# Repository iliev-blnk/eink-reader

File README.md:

# Cititor de cărți electronice cu e-ink

Proiect de licență, Universitatea „Ștefan cel Mare” din Suceava. Beleniuc Ilie, 2027.

Un cititor de cărți electronice cu ecran e-ink de 3,7″ și ESP32-S3, cu firmware
propriu, un format de carte propriu și placa lui proprie.

## Ce e aici

| dosar | ce e |
|---|---|
| [`firmware/`](firmware/) | firmware-ul ESP-IDF: driverul panoului, cardul, butoanele, managerul de aplicații, cititorul, somnul |
| [`spec/`](spec/) | formatul de carte (`.ibv`) și formatul de font (`.ibf`) |
| [`tools/`](tools/) | convertorul EPUB / FB2 / TXT → `.ibv`, unealta de fonturi, comparația cu TeX, fuzzerele, analiza jurnalului de timpi, înregistratorul de curent |
| [`sim/`](sim/) | simulatorul pe PC, cu testele cu imagini de referință |
| [`emu/`](emu/) | emulatorul: firmware-ul adevărat pe un ESP32-S3 emulat (QEMU) |
| [`hardware/`](hardware/) | schema prototipului, desenul plăcii de prototipare (`proto/`) și placa proprie (`pcb/`) |
| [`enclosure/`](enclosure/) | carcasa: model OpenSCAD parametric, cu placa citită din fișierul KiCad |
| [`measurements/`](measurements/) | experimentele: fișele de metodă, datele, figurile și rezultatele (E5 și E6 rulate până acum) |
| [`docs/`](docs/) | planul general, descrierea proiectului și jurnalul |

Planul, cu ce e gata și ce urmează: [`docs/MASTER-PLAN.md`](docs/MASTER-PLAN.md).
Jurnalul: [`docs/README.md`](docs/README.md).

## Unde e

Firmware-ul se compilează și rulează în emulator și în simulator. Încă n-a rulat
pe hardware: prototipul nu e lipit. Placa proprie e o ciornă, nerevizuită și
necomandată.

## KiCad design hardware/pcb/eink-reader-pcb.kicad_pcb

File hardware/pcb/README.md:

# Placa proprie v1 (CIORNĂ)

Placa cititorului care înlocuiește DevKit-ul și firele de pe masă: ESP32-S3,
încărcarea LiPo din USB-C, 3,3 V cu consum mic în somn, cardul și afișajul cu
alimentare comutată, trei butoane. Totul e **generat din script**: piesele și
legăturile sunt scrise o dată în `circuit.py`, din care ies schema, placa așezată
și trasată, verificările și fișierele pentru fabrică.

**E o ciornă.** Are revizia pe hârtie încheiată (PCB-4, [`REVIEW.md`](REVIEW.md));
nu s-a comandat. Codurile LCSC sunt verificate în catalog (PCB-5, mai jos); rotațiile și originile din `cpl.csv` sunt calculate din amprentele EasyEDA, dar nu sunt încă văzute în previzualizarea JLCPCB. Pașii PCB-1…3 din `docs/MASTER-PLAN.md` au acum o
primă variantă completă, cu trei luni înainte de calendar; prototipul de pe
DevKit rămâne referința până la măsurători.

## Cum se rulează

    hardware/pcb/make.sh                  # tot, ~2 min
    hardware/pcb/make.sh --fara-trasare   # doar verificările, fab/ și imaginile

Are nevoie de KiCad 10 (`kicad-cli` și modulul Python `pcbnew`), `cc` și `zip`.
`make.sh` se oprește dacă ERC-ul sau DRC-ul are vreo eroare, vreo legătură lipsă
sau vreo diferență între schemă și placă.

| fișier | ce face |
|---|---|
| `circuit.py` | sursa unică: piesele, valorile, amprentele, pinii pe rețele, codurile LCSC/MPN |
| `gen_sch.py` | schema `eink-reader-pcb.kicad_sch`, grupată pe blocuri, cu etichete globale |
| `gen_pcb.py` | placa: conturul, așezarea, rețelele, planurile, trasarea, umplerea zonelor |
| `route.py`, `astar.c` | trasorul (mai jos) |
| `project.py` | `.kicad_pro`: clasele de rețele și regulile |
| `eink-reader-pcb.kicad_dru` | regulile în plus (găurile butoanelor și ale mufei USB, traseele de putere) |
| `marking.py`, `usv_sigla.json` | serigrafia de pe spate: sigla USV și numele proiectului (mai jos) |
| `verifica.py` | regulile de proiectare pe care ERC/DRC nu le au: pinii ESP32-S3, polaritatea, decuplarea, antena, pinii din firmware (`--pini`: tabelul pin → rețea) |
| `REVIEW.md` | revizia PCB-4: fiecare bloc față de foaia lui de catalog, plus ce rămâne de hotărât |
| `jlc_rotatii.py`, `jlc_corectii.csv`, `test_jlc_rotatii.py` | corecțiile de rotație și origine pentru CPL, din amprentele EasyEDA, și verificarea lor pe o placă cu rotațiile confirmate de JLCPCB (vezi „Comanda”) |
| `make.sh` | tot lanțul, cu verificările |

Ies: `build/` (rapoartele ERC/DRC în JSON, poziții, BOM brut, `cupru.svg`),
`fab/` (gerbere + găuri în `gerber.zip`, `bom.csv` și `cpl.csv` în formatul
JLCPCB) și `img/`. `build/` și `fab/` nu intră în git; se refac oricând.

Schema și placa se deschid normal în KiCad, dar **nu se editează de mână**: o
schimbare se face în `circuit.py` sau în așezarea din `gen_pcb.py` și se rulează
din nou `make.sh`.

## Placa

- 105,79 × 53,80 mm, exact placa modulului de afișaj WeAct de 3,7 țoli, cu
  găurile de M2 în aceleași locuri: cele două stau spate în spate, cu
  distanțiere.
- 4 straturi (procesul JLCPCB): F.Cu semnale, In1.Cu plan GND întreg, In2.Cu
  plan +3V3, B.Cu semnale. Pe F.Cu și B.Cu, GND turnat în rest.
- Trasee și spații de 0,15 mm (procesul permite 0,1), via 0,6/0,3 mm.
  Rețelele de putere (VBUS, VSYS, VBAT, BAT_J, LX1, LX2, 3V3_SD, 3V3_EPD) au
  0,4 mm, cu 0,25 mm admis unde nu încape altfel (mai jos).
- Antena modulului ESP32 e pe marginea din dreapta; pe ultimii 6 mm ai plăcii
  (zona interzisă din amprenta modulului) nu e cupru pe niciun strat.

## Serigrafia

Pe spate (B.SilkS), fața fără piese: sigla Universității „Ștefan cel Mare” din
Suceava, „Proiect de licență”, numele, titlul și „2027 · placa v1”. Sigla e cea
de pe usv.ro, vectorizată cu potrace în `usv_sigla.json`. `marking.py` o pune
într-un grup care se înlocuiește la fiecare rulare (`python3 marking.py` merge și
pe placa deja trasată) și se oprește dacă ceva atinge o pastilă, o gaură sau o via.
Pe față nu e serigrafie în afară de contururile amprentelor: numele pieselor
stau pe F.Fab.

## Piesele

Codurile LCSC sunt verificate în catalogul JLCPCB (secțiunea „Comanda”);
fără cod au rămas doar baretele J3 și J5, care se lipesc de mână.

| bloc | piese | de ce |
|---|---|---|
| USB-C | J1 GCT USB4105, R1/R2 5,1 kΩ pe CC, U1 USBLC6-2SC6 (LCSC C7519), R17/R18 470 kΩ divizor VBUS → IO2 cu C17 100 nF, R25/R26 22 Ω serie pe D+/D− lângă modul | 5 V de la orice încărcător C; ESD pe D+/D−; firmware-ul vede când e cablul pus |
| încărcătorul | U2 BQ24074 (VQFN-16), R3 3,3 kΩ (ILIM ≈ 0,47 A), R4 1,8 kΩ (ICHG ≈ 0,5 A), R5 10 kΩ pe TS, D1/D2 PGOOD/CHG | power-path: dispozitivul merge din USB cu bateria goală; EN1/EN2 legați pentru USB500 |
| bateria | J2 JST-PH 2 pini, JP1 punte de lipit (I_BAT), U6 MAX17048 (indicator ModelGauge, I2C), R15/R16 1 MΩ divizor VBAT → IO1 | JP1 tăiată = un ampermetru în serie cu bateria, pentru E3/E4 |
| 3,3 V | SW1 PCM12 (comutator pornit/oprit pe EN), U3 TPS63900 buck-boost, L1 2,2 µH, R8/R9 configurarea | 75 nA în gol și buck-boost: 3,3 V stabil de la 4,2 V până la 2,5 V din baterie |
| comutatoare de sarcină | U4/U5 TPS22917 pentru card (3V3_SD) și afișaj (3V3_EPD), C7/C8 1 nF urcare lentă, R10/R11 1 MΩ pe EN | cardul și panoul nu consumă nimic în somn |
| MCU | U7 ESP32-S3-WROOM-1-N16R8 (C2913202), RC pe EN, SW5 BOOT, SW6 RESET, J5 UART0 | același modul ca pe DevKit, deci aceeași hartă de pini |
| butoane | SW2–SW4 Alps SKRTLAE010 (C110293), pe margini (două pe stânga, MENIU sus), apăsate din lateral | ÎNAPOI, ÎNAINTE, MENIU |
| afișaj | J3 baretă 1×8 de 2,54 mm spre modulul WeAct | BUSY, RST, DC, CS, SCK, MOSI, GND, 3V3_EPD; SCK și MOSI sunt ale lui, nu le împarte cu cardul |
| card | J4 Molex 104031 microSD, R21–R24 47 kΩ | modul SPI; pull-up pe CS, MISO și DAT1/DAT2 |
| test | TP1–TP8: VBUS, VSYS, BAT_J, VBAT, +3V3, GND, 3V3_SD, 3V3_EPD | pentru punerea în funcțiune și măsurători, într-un singur rând |

GPIO-urile păstrează harta de pe DevKit (`firmware/boards/include/board_devkit.h`); antetul plăcii
e `firmware/boards/include/board_pcb_v1.h`, verificat de `verifica.py`. În plus față de DevKit:
I2C pe IO16 (SDA) și IO17 (SCL), FG_ALRT pe IO7, SD_PWR_EN pe IO15,
EPD_PWR_EN pe IO21, VBUS_SENSE pe IO2. Singura diferență: pe DevKit cardul și
panoul împart bus-ul SPI (IO11/12/13); aici bus-ul acela rămâne cardului, iar
panoul are SCK pe IO47 și MOSI pe IO48. Pe N16R8 IO47/IO48 sunt pini obișnuiți
de 3,3 V (doar modulele R16V îi au de 1,8 V).

## Consumul în somn (estimat)

| piesa | curent |
|---|---:|
| ESP32-S3 în somn adânc, cu temporizatorul RTC | ~8 µA |
| BQ24074, din baterie, fără USB | 4,3 µA |
| MAX17048 în hibernare | 3 µA |
| divizorul VBAT (2 MΩ la ~4 V) | 2,1 µA |
| TPS63900 în gol | ~0,1 µA |
| cardul și afișajul (comutatoarele oprite) | ~0 |
| **total** | **~17,5 µA** |

Cifrele sunt din foile de catalog (tipice). Cu o baterie de 1500 mAh, somnul
singur ar ține ani; consumul real e dat de paginile întoarse și se măsoară la
E3/E4, cu JP1 tăiată.

## Trasorul

KiCad nu are un trasor automat, iar FreeRouting cere Java și o rundă de
import/export. `route.py` e un trasor propriu, pe grilă, cu căutarea în C
(`astar.c`, prin ctypes):

- Grilă de 0,125 mm pe F.Cu și B.Cu, câte o matrice pe clasă de lățime (0,15 / 0,25 / 0,4 mm, via). Pentru fiecare rețea, cuprul celorlalte e
  umflat cu jumătatea lățimii pistei plus distanța minimă și scos din grilă,
  deci ce găsește A* respectă DRC-ul prin construcție.
- A* cu euristică octilă, via cu cost, B.Cu puțin mai scump (rămâne loc pentru turnarea GND). O rețea
  cu mai mulți pini crește ca un arbore: fiecare pin nou caută cel mai apropiat
  punct al arborelui de până acum.
- Pinii SMD de pe GND și +3V3 primesc o scurtă ieșire spre o via în planul lor.
- **Smulgere și retrasare** (în felul PathFinder): după 6 treceri complete în
  ordini diferite, o rețea care nu încape se caută din nou „moale”, având voie
  să treacă peste cuprul altora cu un cost mare. Rețelele atinse de drumul găsit
  se smulg, ea se trasează, apoi ele se retrasează. Celulele disputate primesc
  un cost istoric care crește, ca rețelele să nu se smulgă una pe alta la
  nesfârșit.

Rezultatul, pe placa de acum: **52 din 52 de rețele trasate**, 0 ieșiri spre
plan eșuate, după 14 smulgeri. 1.022 de segmente, 1.469,3 mm de pistă, 206 via.

## Verificările

`make.sh`, pe placa din git:

- ERC: 0.
- DRC (regulile din `.kicad_pro` și `.kicad_dru`, cu zonele reumplute): 0
  erori, 0 legături lipsă, 0 diferențe între schemă și placă.
- 4 avertismente `lib_footprint_mismatch` (U2, U3, U7, SW1): amprentele diferă
  de biblioteca KiCad dinadins. La U2 și U3 viaurile termice din padul central
  sunt mărite la găuri de 0,3 mm (minimul fabricii) și rărite. La U7 curtea e
  tăiată la marginea plăcii, unde iese antena. La SW1 serigrafia de peste
  margine e scoasă.

Pistele de putere de 0,25 mm (unde 0,4 nu încape):

| rețea | lățime | lungime | curent |
|---|---|---:|---|
| LX2 | 0,25 mm | 4,6 mm | nodul de comutație al TPS63900, sub 0,5 A |
| VBUS | 0,25 mm | 71,1 mm | de la J1 la U2, U1, R17 și TP1: curentul de intrare al încărcătorului, ≤ 0,5 A (modul USB500), ~0,14 Ω, deci ~70 mV cădere din cei 5 V |

O pistă de 0,25 mm în cupru de 1 oz duce ~1 A la o încălzire de 10 °C, deci
are rezervă de două ori. Celelalte rețele de putere sunt de 0,4 mm: VSYS
58,6 mm, 3V3_EPD 31,8 mm, 3V3_SD 42,8 mm, BAT_J 13,8 mm, LX1 1,7 mm, VBAT 51,9 mm.

## De știut înainte de comandă

- **Poziția baretei J3** e luată din desenul modulului WeAct. Se măsoară pe
  modulul adevărat înainte de comandă.
- **Polaritatea JST** nu e standard: pinul 1 e plusul aici, dar cablurile
  bateriilor vin în ambele feluri. Se verifică cu multimetrul înainte de prima
  conectare.
- **Alimentarea inversă**: înainte de a opri 3V3_SD sau 3V3_EPD, firmware-ul
  trebuie să pună liniile SPI și CS-urile pe 0, altfel cardul sau panoul se
  alimentează prin diodele de protecție ale pinilor. O face `board_power_off()`
  din `firmware/main/board_io.c` (PCB-8), netestat pe placă. Cum fiecare are bus-ul lui, liniile unuia se pun
  pe 0 fără să-l încurce pe celălalt (`REVIEW.md`, punctul 1).
- **TPS63900 la vârfurile de WiFi**: dă până la ~400 mA; ESP32-S3 cere vârfuri
  de ~350 mA la transmisie. Merge cu C5 + C14 (2 × 22 µF), dar fără rezervă.
  Hotărât (`REVIEW.md`, punctul 4): firmware-ul limitează emisia la 13 dBm și
  pornește WiFi-ul doar cu panoul și cardul inactive. Cititorul nu are încă
  WiFi; vârfurile se măsoară pe placă.
- **Decuparea sub antenă** e amânată până la măsurătoarea de semnal din
  carcasă (ENC-3; `REVIEW.md`, punctul 3).
- **TS cu rezistor fix**: R5 îi spune încărcătorului că bateria are mereu
  25 °C, deci nu oprește încărcarea la cald sau la rece. Bateria trebuie să aibă
  protecția ei (PCM), ca toate celulele LiPo din comerț.
- **R8/R9** sunt verificate în tabelele 7-2/7-3 ale foii TPS63900 (`REVIEW.md`).
- Contactul de detecție al cardului (J4) nu e folosit.
- J2, J3, J5 sunt cu găuri (THT); SW2–SW4 și J1 au picioare de fixare în găuri
  nemetalizate, cu reguli de distanță proprii în `.kicad_dru`.
- Etichetele pieselor sunt pe F.Fab, nu pe serigrafie: placa e plină, iar
  pozițiile se văd în `build/cupru.svg`.
- **Rotațiile din `cpl.csv`** sunt calculate, nu confirmate în previzualizare: vezi „Comanda”.

## Comanda (PCB-5)

Codurile din `circuit.py` sunt verificate pe 2026-11-19 în catalogul de
asamblare JLCPCB: modelul, capsula și stocul fiecăruia. Stocul e cel din acea zi
și se schimbă. „Necesar” înseamnă 5 plăci, fără pierderile de la montaj.

| Piese | LCSC | Model | Tip | Stoc | Necesar |
|---|---|---|---|---:|---:|
| C1, C16 | C15849 | Samsung CL10A105KB8NNNC, 1 µF 50 V X5R | de bază | 12.258.861 | 10 |
| C2, C3 | C19666 | Samsung CL10A475KO8NNNC, 4,7 µF 16 V X5R | de bază | 3.307.574 | 10 |
| C4, C9, C11 | C19702 | Samsung CL10A106KP8NNNC, 10 µF 10 V X5R | de bază | 10.685.497 | 15 |
| C5, C14 | C59461 | Samsung CL10A226MQ8NRNC, 22 µF 6,3 V X5R | de bază | 5.997.547 | 10 |
| C7, C8 | C1588 | Samsung CL10B102KB8NNNC, 1 nF 50 V X7R | de bază | 5.287.619 | 10 |
| C10, C12, C13, C15, C17 | C14663 | YAGEO CC0603KRX7R9BB104, 100 nF 50 V X7R | de bază | 53.069.967 | 25 |
| D1 | C12624 | KENTO KT-0603G, verde | extinsă | 208.308 | 5 |
| D2 | C111340 | KENTO KT-0603O, portocaliu | extinsă | 16.346 | 5 |
| J1 | C3020560 | GCT USB4105-GF-A | extinsă | 13.662 | 5 |
| J2 | C131337 | JST B2B-PH-K-S (THT) | extinsă | 273.875 | 5 |
| J4 | C585350 | Molex 104031-0811 | extinsă | 46.266 | 5 |
| L1 | C488330 | Murata DFE252010F-2R2M | extinsă | 4.113 | 5 |
| R1, R2 | C23186 | UNI-ROYAL 0603WAF5101T5E, 5,1 kΩ | de bază | 18.766.089 | 10 |
| R3 | C22978 | UNI-ROYAL 0603WAF3301T5E, 3,3 kΩ | de bază | 4.161.647 | 5 |
| R4 | C4177 | UNI-ROYAL 0603WAF1801T5E, 1,8 kΩ | de bază | 479.075 | 5 |
| R5, R19, R20 | C25804 | UNI-ROYAL 0603WAF1002T5E, 10 kΩ | de bază | 43.980.846 | 15 |
| R6, R7 | C21190 | UNI-ROYAL 0603WAF1001T5E, 1 kΩ | de bază | 31.275.885 | 10 |
| R8 | C23029 | UNI-ROYAL 0603WAF3652T5E, 36,5 kΩ | extinsă | 40.313 | 5 |
| R9 | C22885 | UNI-ROYAL 0603WAF1622T5E, 16,2 kΩ | extinsă | 46.486 | 5 |
| R10, R11, R15, R16 | C22935 | UNI-ROYAL 0603WAF1004T5E, 1 MΩ | de bază | 5.254.394 | 20 |
| R12, R13 | C23162 | UNI-ROYAL 0603WAF4701T5E, 4,7 kΩ | de bază | 16.140.631 | 10 |
| R14 | C25803 | UNI-ROYAL 0603WAF1003T5E, 100 kΩ | de bază | 13.730.726 | 5 |
| R17, R18 | C23178 | UNI-ROYAL 0603WAF4703T5E, 470 kΩ | de bază | 1.015.624 | 10 |
| R21–R24 | C25819 | UNI-ROYAL 0603WAF4702T5E, 47 kΩ | de bază | 2.513.903 | 20 |
| R25, R26 | C23345 | UNI-ROYAL 0603WAF220JT5E, 22 Ω | de bază | 4.794.624 | 10 |
| SW1 | C221841 | C&K PCM12SMTR | extinsă | 7.732 | 5 |
| SW2–SW4 | C110293 | Alps SKRTLAE010 | extinsă | 30.677 | 15 |
| SW5, SW6 | C318884 | XKB TS-1187A-B-A-B | de bază | 762.721 | 10 |
| U1 | C7519 | ST USBLC6-2SC6 | extinsă | 33.704 | 5 |
| U2 | C54313 | TI BQ24074RGTR | extinsă | 3.319 | 5 |
| U3 | C1518762 | TI TPS63900DSKR | extinsă | 10.658 | 5 |
| U4, U5 | C2681320 | TI TPS22917DBVR | extinsă | 18.662 | 10 |
| U6 | C2682616 | Analog Devices MAX17048G+T10 | extinsă | 25.314 | 5 |
| U7 | C2913202 | Espressif ESP32-S3-WROOM-1-N16R8 | extinsă | 8.519 | 5 |

Ce s-a schimbat față de lista din PCB-1:

- **LED-urile.** Everlight C72043 (verde) și C72038 nu mai au stoc; C72038 era
  galben, nu portocaliu. Le iau locul KENTO KT-0603G și KT-0603O. Verdele are
  ~3,1 V în direct. Prin R6 de 1 kΩ, de la VSYS (peste ~4,2 V cu cablul pus),
  îi rămâne ~1 mA, destul pentru un indicator.
- **BOOT și RESET.** C318884 nu e C&K, ci XKB TS-1187A (5,1 × 5,1 mm). Desenul
  XKB recomandă pastile de 1,0 × 0,75 mm, cu centrele la ±3,0 și ±1,875 mm, iar
  perechile A–B și C–D sunt legate între ele. Amprenta TL3342 are pastile de
  1,7 × 1,0 la ±3,15 și ±1,9, cu pinul 1 sus și 2 jos. Pastilele XKB intră
  întregi în cele KiCad, iar perechile se potrivesc, deci amprenta rămâne.
- **BQ24074.** JLCPCB are BQ24074RGTR (C54313). Nu spune dacă vine în capsula
  RGT0016B sau RGT0016C, dar amprenta merge cu amândouă (`REVIEW.md`, U2).

În tabel sunt 16 piese extinse distincte (SW2–SW4 contează o dată); JLCPCB
taxează separat fiecare piesă extinsă dintr-o comandă. J2 e cu găuri, iar J3 și
J5 nu au cod: toate trei se lipesc de mână (PCB-6), deci la montaj rămân 15
piese extinse. Orice altă piesă scoasă din `cpl.csv` se lipește tot de mână.

**Rotațiile și originile.** JLCPCB așază fiecare piesă după amprenta EasyEDA a
codului LCSC, nu după amprenta KiCad, iar cele două pot avea pinul 1 în alt colț
și altă origine. `jlc_rotatii.py` suprapune, pentru fiecare piesă cu cod, padurile
din KiCad peste cele din EasyEDA. Unde ambele numerotează la fel, decid numerele
(potrivire Kabsch, rotunjită la 90°), iar o nepotrivire oprește piesa. Unde
numerotarea diferă (SW1–SW6, J1, J4, padul expus al lui U2 și U3, desenat din alt
număr de paduri) se încearcă cele patru rotații geometric. O rotație trece dacă
fiecare pad se suprapune cu perechea lui (centrul unuia în cuprul celuilalt): un
prag de distanță între centre nu merge, EasyEDA desenează des padurile mai lungi.
La LED-uri și diode catodul se ia după semnul „+” din amprenta EasyEDA, după care
se ia și previzualizarea JLCPCB, nu după numărul pinului, care diferă între
biblioteci. Rotația găsită și originea EasyEDA adusă în cadrul KiCad merg în
`jlc_corectii.csv`, pe care `make.sh` îl aplică la `cpl.csv` și pe care îl
refuză dacă nu mai corespunde plăcii (cod sau amprentă schimbate). Datele EasyEDA
se descarcă în `build/easyeda/` (`python3 jlc_rotatii.py --descarca`) și nu intră
în depozit.

Metoda e verificată pe placa de test a proiectului kicad-jlcpcb-tools, care are
rotațiile observate în previzualizarea JLCPCB pentru 47 de piese
(`tests/fixtures/jlcfootprint/truth.csv`, cu răspunsurile EasyEDA înregistrate):
`python3 test_jlc_rotatii.py <clona>` dă 46 corecte, 0 greșite (D5 e scoasă,
polaritatea ei e greșită intenționat). Placa are cazurile grele: LED-uri cu anodul
pe pinul 1 în EasyEDA, o diodă la care simbolul EasyEDA contrazice semnul „+”,
SOT-23 -CW, care trebuie refuzat, SOT-223 cu tabul numerotat diferit.

Toate cele 61 de piese ale noastre se potrivesc. Pentru circuitele integrate cu
colțul pinului 1 în numele pachetului EasyEDA, rotația iese aceeași (TL 0°, BL
270°, BR 180°): U1 și U6 270°, U4 și U5 180°, U2 și U3 0°; U7 (modulul ESP32) nu
are colț în nume și iese 0°. D1 și D2 au catodul pe pinul 1 și în EasyEDA, deci
0°. Originile contează la U7, mutat cu 3,62 mm (originea amprentei KiCad nu e în
centrul padurilor), la J1 (1,30 mm) și la J2 (1 mm, pinul 1 față de centru). La
J4, pinii 1–8 cad pe ei înșiși, iar pinii de detecție a cardului sunt 9–10 în
KiCad și 11–12 în EasyEDA. SW5 și SW6 trec și la 0°, și la 180°: piesa e
simetrică.

În previzualizarea JLCPCB, înainte de plată, se verifică:

| Piese | Ce trebuie să se vadă |
|---|---|
| D1, D2 | catodul pe pastila 1 (rețelele PGOOD_N, CHG_N), după marcajul de catod al piesei |
| U1 | pinul 1 al USBLC6 pe pastila 1: rotit cu 180°, VBUS ajunge pe GND |
| U2, U3, U6 | punctul pinului 1 pe pastila 1, EP-ul centrat |
| U4, U5 | pinul 1 (VIN) pe pastila 1 |
| U7 | antena spre marginea plăcii, peste zona fără cupru |
| J1, J4 | gura conectorului spre marginea plăcii |
| SW1, SW2–SW4 | maneta, respectiv butonul, spre marginea plăcii |
| SW5, SW6, L1, R, C | doar aliniate: 0° și 180° sunt la fel, 90° nu |

O piesă rotită greșit se corectează acolo, în previzualizare, iar cauza se caută
apoi în `jlc_rotatii.py`, ca să n-o repete comanda următoare.

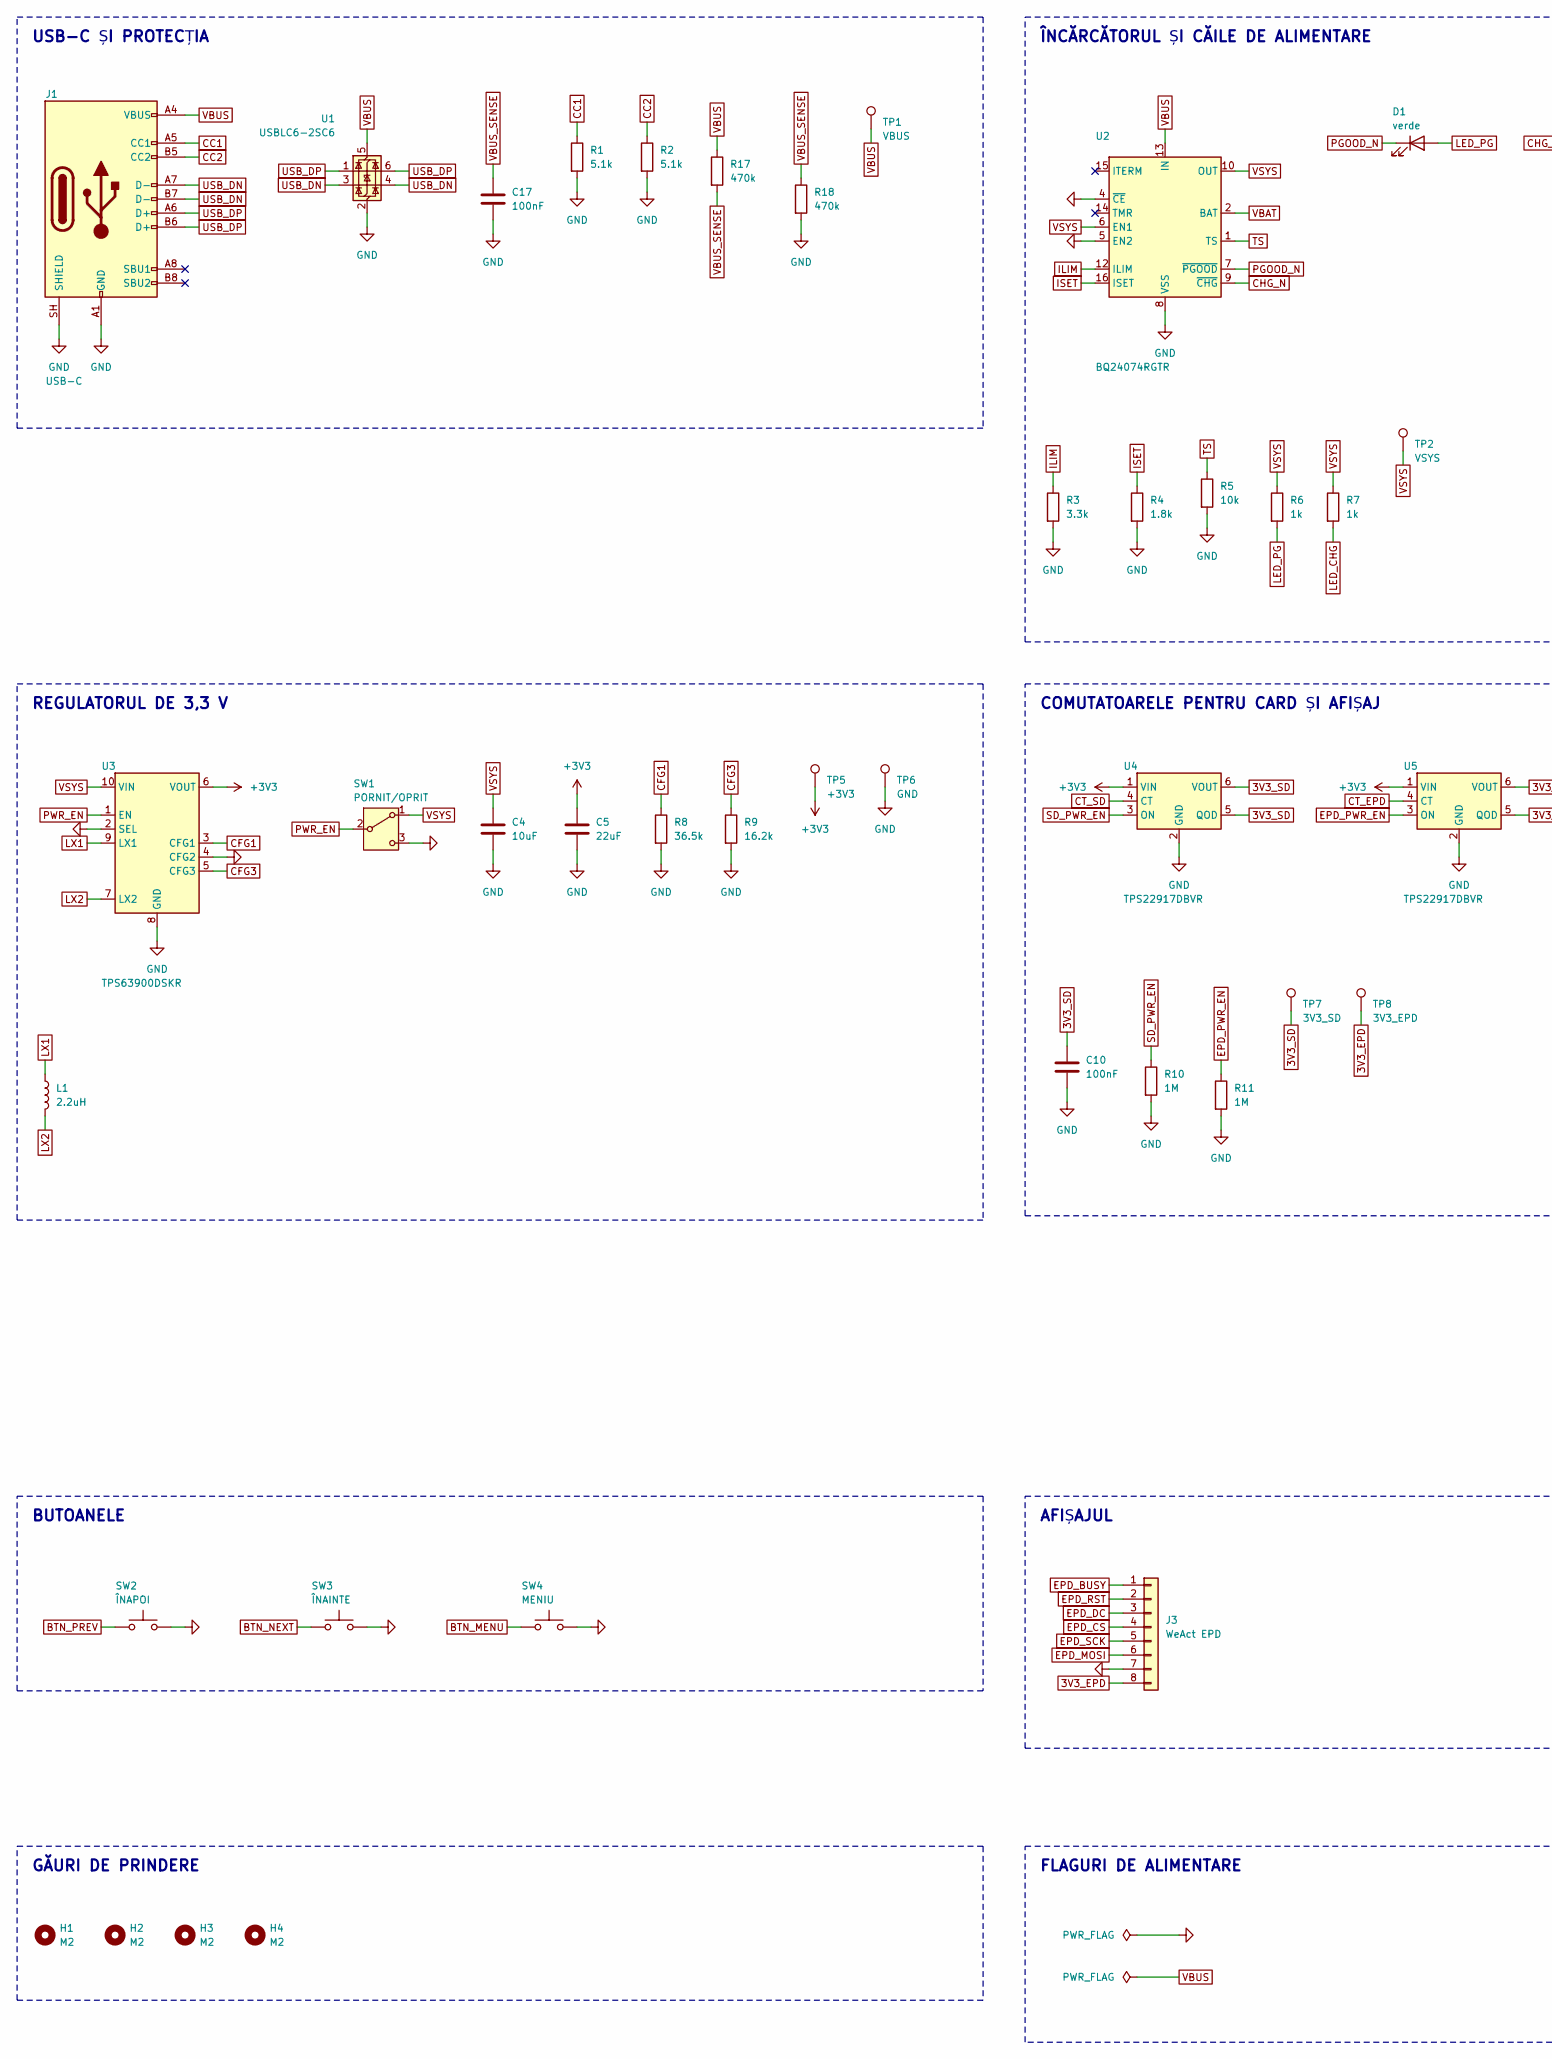
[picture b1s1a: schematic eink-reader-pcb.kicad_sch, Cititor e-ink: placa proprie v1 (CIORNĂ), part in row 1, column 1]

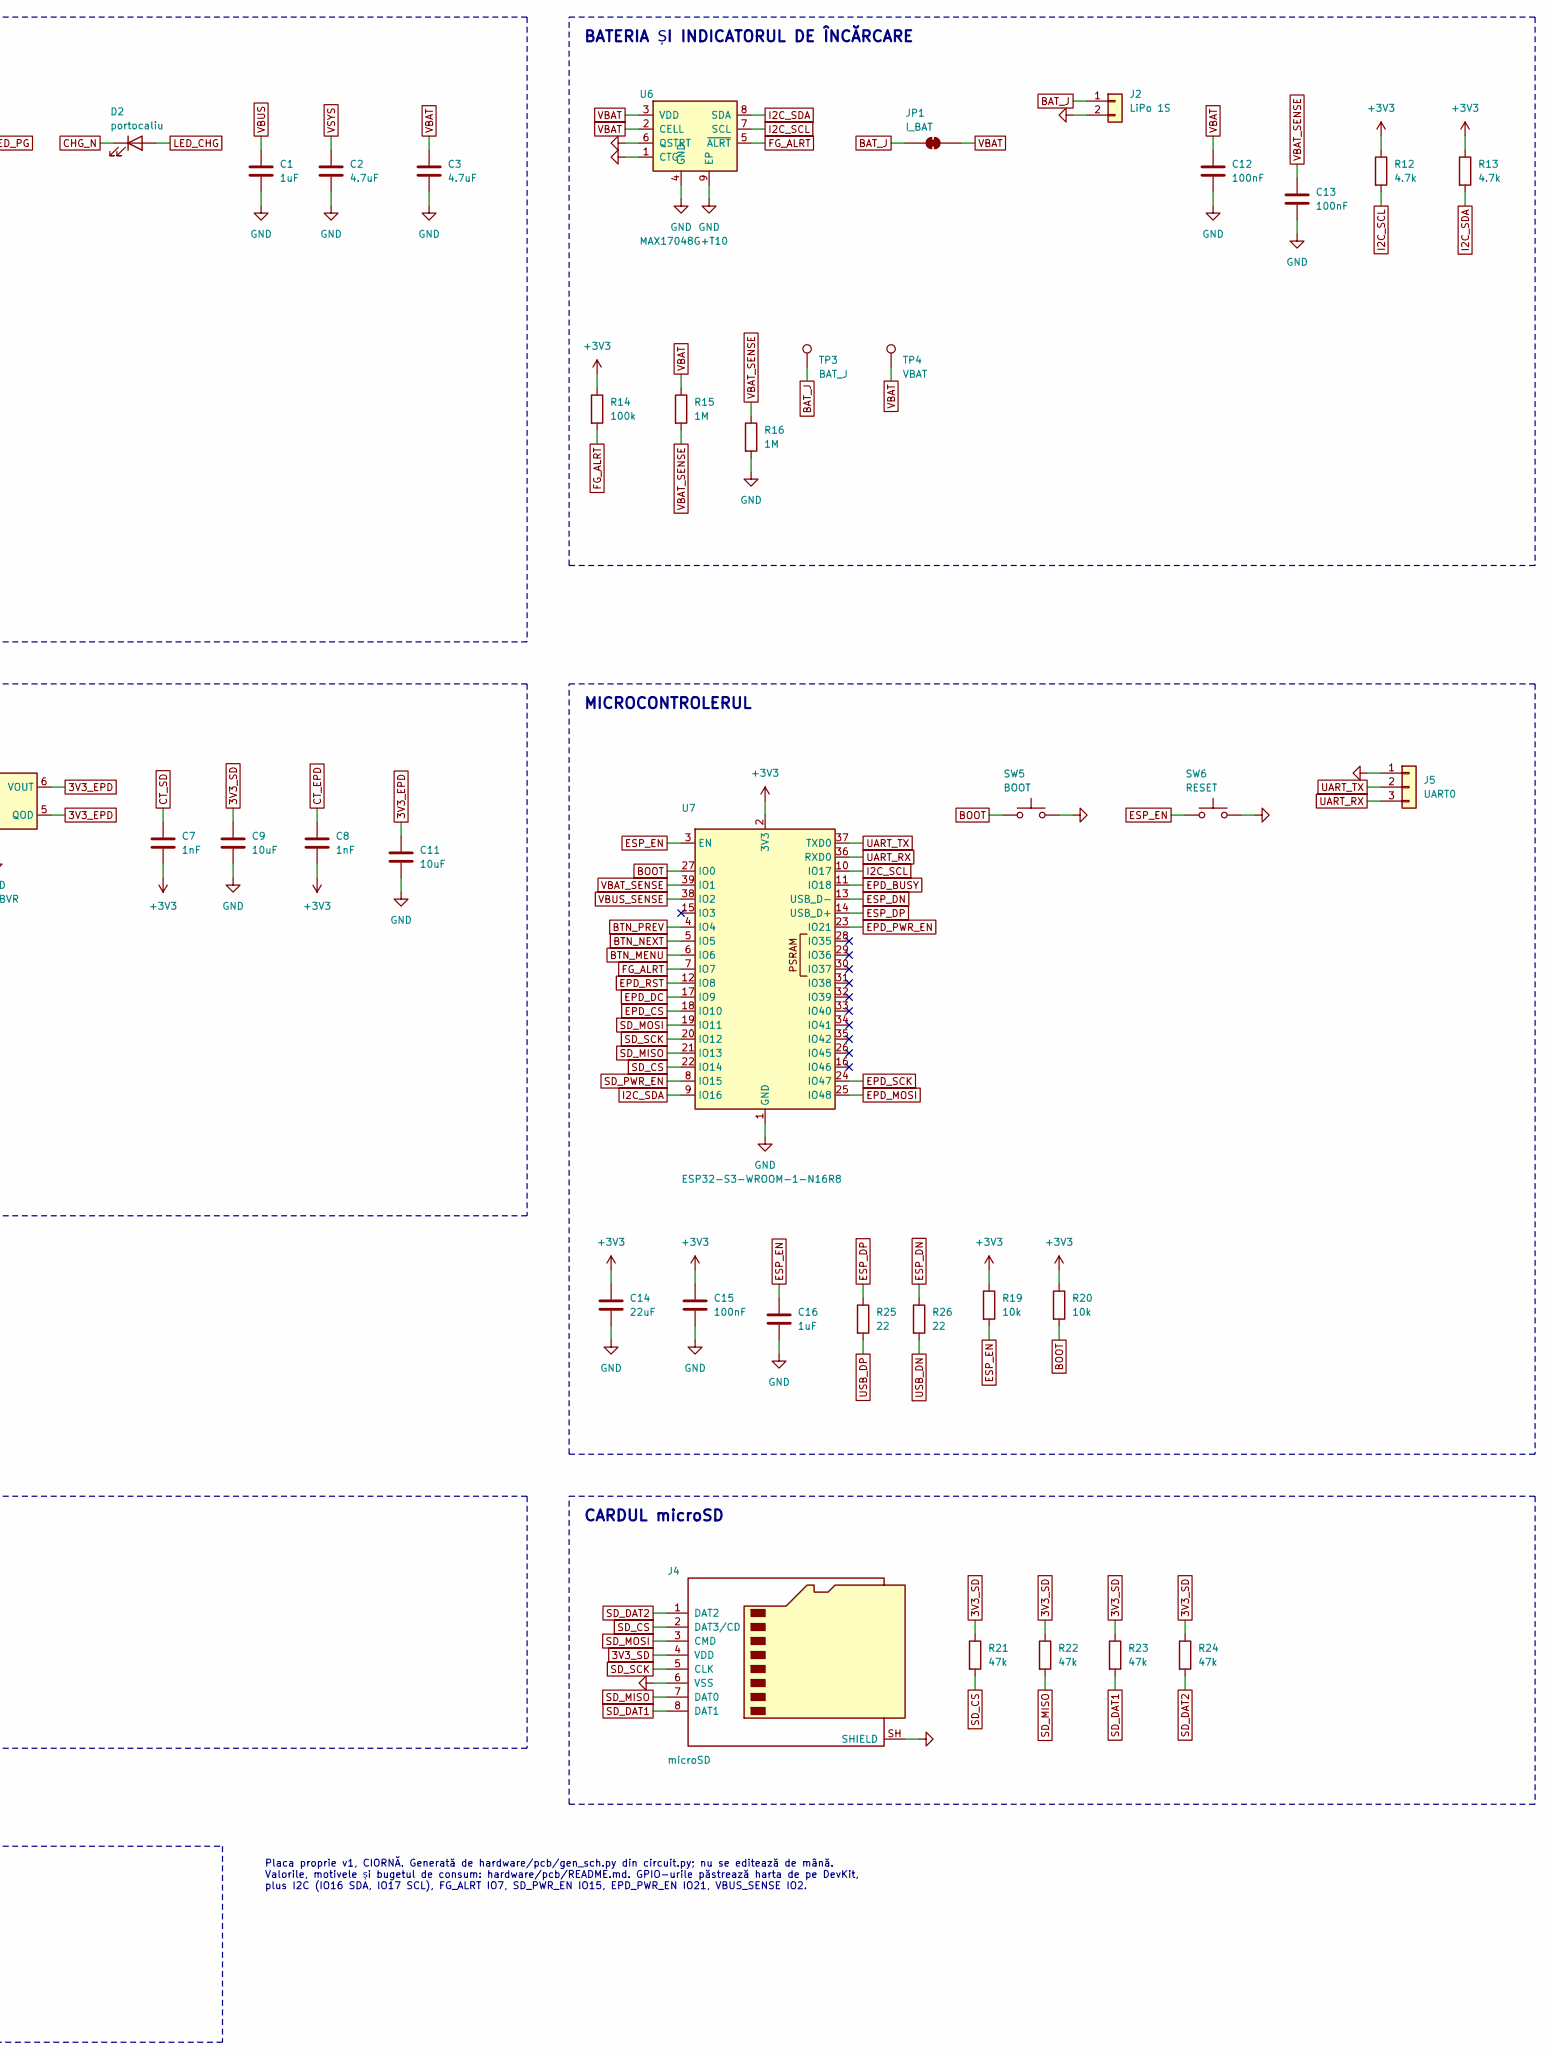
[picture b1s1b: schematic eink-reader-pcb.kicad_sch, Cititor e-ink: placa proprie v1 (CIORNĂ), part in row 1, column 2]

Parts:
C1, C16: 1uF; C_0603_1608Metric; MPN 1uF X5R/X7R 0603; LCSC C15849
C2, C3: 4.7uF; C_0603_1608Metric; MPN 4.7uF X5R/X7R 0603; LCSC C19666
C4, C9, C11: 10uF; C_0603_1608Metric; MPN 10uF X5R/X7R 0603; LCSC C19702
C5, C14: 22uF; C_0603_1608Metric; MPN 22uF X5R/X7R 0603; LCSC C59461
C7, C8: 1nF; C_0603_1608Metric; MPN 1nF X5R/X7R 0603; LCSC C1588
C10, C12, C13, C15, C17: 100nF; C_0603_1608Metric; MPN 100nF X5R/X7R 0603; LCSC C14663
D1: verde; LED_0603_1608Metric; MPN KENTO KT-0603G; LCSC C12624
D2: portocaliu; LED_0603_1608Metric; MPN KENTO KT-0603O; LCSC C111340
H1, H2, H3, H4: M2; MountingHole_2.2mm_M2
J1: USB-C; USB_C_Receptacle_GCT_USB4105-xx-A_16P_TopMnt_Horizontal; MPN GCT USB4105-GF-A; LCSC C3020560
J2: LiPo 1S; JST_PH_B2B-PH-K_1x02_P2.00mm_Vertical; MPN JST B2B-PH-K-S; LCSC C131337
J3: WeAct EPD; PinHeader_1x08_P2.54mm_Vertical
J4: microSD; microSD_HC_Molex_104031-0811; MPN Molex 104031-0811; LCSC C585350
J5: UART0; PinHeader_1x03_P2.54mm_Vertical
JP1: I_BAT; SolderJumper-2_P1.3mm_Bridged_RoundedPad1.0x1.5mm
L1: 2.2uH; L_1008_2520Metric; MPN Murata DFE252010F-2R2M; LCSC C488330
R1, R2: 5.1k; R_0603_1608Metric; MPN 5.1k 1% 0603; LCSC C23186
R3: 3.3k; R_0603_1608Metric; MPN 3.3k 1% 0603; LCSC C22978
R4: 1.8k; R_0603_1608Metric; MPN 1.8k 1% 0603; LCSC C4177
R5, R19, R20: 10k; R_0603_1608Metric; MPN 10k 1% 0603; LCSC C25804
R6, R7: 1k; R_0603_1608Metric; MPN 1k 1% 0603; LCSC C21190
R8: 36.5k; R_0603_1608Metric; MPN 36.5k 1% 0603; LCSC C23029
R9: 16.2k; R_0603_1608Metric; MPN 16.2k 1% 0603; LCSC C22885
R10, R11, R15, R16: 1M; R_0603_1608Metric; MPN 1M 1% 0603; LCSC C22935
R12, R13: 4.7k; R_0603_1608Metric; MPN 4.7k 1% 0603; LCSC C23162
R14: 100k; R_0603_1608Metric; MPN 100k 1% 0603; LCSC C25803
R17, R18: 470k; R_0603_1608Metric; MPN 470k 1% 0603; LCSC C23178
R21, R22, R23, R24: 47k; R_0603_1608Metric; MPN 47k 1% 0603; LCSC C25819
R25, R26: 22; R_0603_1608Metric; MPN 22 1% 0603; LCSC C23345
SW1: PORNIT/OPRIT; SW_SPDT_PCM12; MPN C&K PCM12SMTR; LCSC C221841
SW2: ÎNAPOI; SW_Push_1P1T-MP_NO_Horizontal_Alps_SKRTLAE010; MPN Alps SKRTLAE010; LCSC C110293
SW3: ÎNAINTE; SW_Push_1P1T-MP_NO_Horizontal_Alps_SKRTLAE010; MPN Alps SKRTLAE010; LCSC C110293
SW4: MENIU; SW_Push_1P1T-MP_NO_Horizontal_Alps_SKRTLAE010; MPN Alps SKRTLAE010; LCSC C110293
SW5: BOOT; SW_SPST_TL3342; MPN XKB TS-1187A-B-A-B; LCSC C318884
SW6: RESET; SW_SPST_TL3342; MPN XKB TS-1187A-B-A-B; LCSC C318884
TP1: VBUS; TestPoint_Pad_D1.5mm
TP2: VSYS; TestPoint_Pad_D1.5mm
TP3: BAT_J; TestPoint_Pad_D1.5mm
TP4: VBAT; TestPoint_Pad_D1.5mm
TP5: +3V3; TestPoint_Pad_D1.5mm
TP6: GND; TestPoint_Pad_D1.5mm
TP7: 3V3_SD; TestPoint_Pad_D1.5mm
TP8: 3V3_EPD; TestPoint_Pad_D1.5mm
U1: USBLC6-2SC6; SOT-23-6; MPN ST USBLC6-2SC6; LCSC C7519
U2: BQ24074RGTR; VQFN-16-1EP_3x3mm_P0.5mm_EP1.6x1.6mm_ThermalVias; MPN TI BQ24074RGTR; LCSC C54313
U3: TPS63900DSKR; WSON-10-1EP_2.5x2.5mm_P0.5mm_EP1.2x2mm_ThermalVias; MPN TI TPS63900DSKR; LCSC C1518762
U4, U5: TPS22917DBVR; SOT-23-6; MPN TI TPS22917DBVR; LCSC C2681320
U6: MAX17048G+T10; TDFN-8-1EP_2x2mm_P0.5mm_EP0.8x1.2mm; MPN Analog Devices MAX17048G+T10; LCSC C2682616
U7: ESP32-S3-WROOM-1-N16R8; ESP32-S3-WROOM-1; MPN Espressif ESP32-S3-WROOM-1-N16R8; LCSC C2913202

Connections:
3V3_EPD: C11.1, J3.8, TP8.1, U5.5 (QOD), U5.6 (VOUT)
3V3_SD: C9.1, C10.1, J4.4 (VDD), R21.1, R22.1, R23.1, R24.1, TP7.1, U4.5 (QOD), U4.6 (VOUT)
+3V3: C5.1, C7.2, C8.2, C14.1, C15.1, R12.1, R13.1, R14.1, R19.1, R20.1, TP5.1, U3.6 (VOUT), U4.1 (VIN), U5.1 (VIN), U7.2 (3V3)
BAT_J: J2.1, JP1.1 (A), TP3.1
BOOT: R20.2, SW5.1, U7.27 (IO0)
BTN_MENU: SW4.1, U7.6 (IO6)
BTN_NEXT: SW3.1, U7.5 (IO5)
BTN_PREV: SW2.1, U7.4 (IO4)
CC1: J1.A5 (CC1), R1.1
CC2: J1.B5 (CC2), R2.1
CFG1: R8.1, U3.3 (CFG1)
CFG3: R9.1, U3.5 (CFG3)
CHG_N: D2.1 (K), U2.9 (~CHG)
CT_EPD: C8.1, U5.4 (CT)
CT_SD: C7.1, U4.4 (CT)
EPD_BUSY: J3.1, U7.11 (IO18)
EPD_CS: J3.4, U7.18 (IO10)
EPD_DC: J3.3, U7.17 (IO9)
EPD_MOSI: J3.6, U7.25 (IO48)
EPD_PWR_EN: R11.1, U5.3 (ON), U7.23 (IO21)
EPD_RST: J3.2, U7.12 (IO8)
EPD_SCK: J3.5, U7.24 (IO47)
ESP_DN: R26.1, U7.13 (USB_D-)
ESP_DP: R25.1, U7.14 (USB_D+)
ESP_EN: C16.1, R19.2, SW6.1, U7.3 (EN)
FG_ALRT: R14.2, U6.5 (~ALRT), U7.7 (IO7)
GND: C1.2, C2.2, C3.2, C4.2, C5.2, C9.2, C10.2, C11.2, C12.2, C13.2, C14.2, C15.2, C16.2, C17.2, J1.A1 (GND), J1.A12 (GND), J1.B1 (GND), J1.B12 (GND), J1.SH (SHIELD), J2.2, J3.7, J4.6 (VSS), J4.SH (SHIELD), J5.1, R1.2, R2.2, R3.2, R4.2, R5.2, R8.2, R9.2, R10.2, R11.2, R16.2, R18.2, SW1.3 (C), SW2.2, SW3.2, SW4.2, SW5.2, SW6.2, TP6.1, U1.2 (GND), U2.4 (~CE), U2.5 (EN2), U2.8 (VSS), U2.17 (VSS), U3.2 (SEL), U3.4 (CFG2), U3.8 (GND), U3.11 (GND), U4.2 (GND), U5.2 (GND), U6.1 (CTG), U6.4 (GND), U6.6 (QSTRT), U6.9 (EP), U7.1 (GND), U7.40 (GND), U7.41 (GND)
I2C_SCL: R12.2, U6.7 (SCL), U7.10 (IO17)
I2C_SDA: R13.2, U6.8 (SDA), U7.9 (IO16)
ILIM: R3.1, U2.12 (ILIM)
ISET: R4.1, U2.16 (ISET)
LED_CHG: D2.2 (A), R7.2
LED_PG: D1.2 (A), R6.2
LX1: L1.1, U3.9 (LX1)
LX2: L1.2, U3.7 (LX2)
PGOOD_N: D1.1 (K), U2.7 (~PGOOD)
PWR_EN: SW1.2 (B), U3.1 (EN)
SD_CS: J4.2 (DAT3/CD), R21.2, U7.22 (IO14)
SD_DAT1: J4.8 (DAT1), R23.2
SD_DAT2: J4.1 (DAT2), R24.2
SD_MISO: J4.7 (DAT0), R22.2, U7.21 (IO13)
SD_MOSI: J4.3 (CMD), U7.19 (IO11)
SD_PWR_EN: R10.1, U4.3 (ON), U7.8 (IO15)
SD_SCK: J4.5 (CLK), U7.20 (IO12)
TS: R5.1, U2.1 (TS)
UART_RX: J5.3, U7.36 (RXD0)
UART_TX: J5.2, U7.37 (TXD0)
USB_DN: J1.A7 (D-), J1.B7 (D-), R26.2, U1.3 (I/O2), U1.4 (I/O2)
USB_DP: J1.A6 (D+), J1.B6 (D+), R25.2, U1.1 (I/O1), U1.6 (I/O1)
VBAT: C3.1, C12.1, JP1.2 (B), R15.1, TP4.1, U2.2 (BAT), U2.3 (BAT), U6.2 (CELL), U6.3 (VDD)
VBAT_SENSE: C13.1, R15.2, R16.1, U7.39 (IO1)
VBUS: C1.1, J1.A4 (VBUS), J1.A9 (VBUS), J1.B4 (VBUS), J1.B9 (VBUS), R17.1, TP1.1, U1.5 (VBUS), U2.13 (IN)
VBUS_SENSE: C17.1, R17.2, R18.1, U7.38 (IO2)
VSYS: C2.1, C4.1, R6.1, R7.1, SW1.1 (A), TP2.1, U2.6 (EN1), U2.10 (OUT), U2.11 (OUT), U3.10 (VIN)

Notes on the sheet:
USB-C ȘI PROTECȚIA
ÎNCĂRCĂTORUL ȘI CĂILE DE ALIMENTARE
BATERIA ȘI INDICATORUL DE ÎNCĂRCARE
REGULATORUL DE 3,3 V
COMUTATOARELE PENTRU CARD ȘI AFIȘAJ
MICROCONTROLERUL
BUTOANELE
AFIȘAJUL
CARDUL microSD
GĂURI DE PRINDERE
FLAGURI DE ALIMENTARE
Placa proprie v1, CIORNĂ. Generată de hardware/pcb/gen_sch.py din circuit.py; nu se editează de mână. Valorile, motivele și bugetul de consum: hardware/pcb/README.md. GPIO-urile păstrează harta de pe DevKit, plus I2C (IO16 SDA, IO17 SCL), FG_ALRT IO7, SD_PWR_EN IO15, EPD_PWR_EN IO21, VBUS_SENSE IO2.

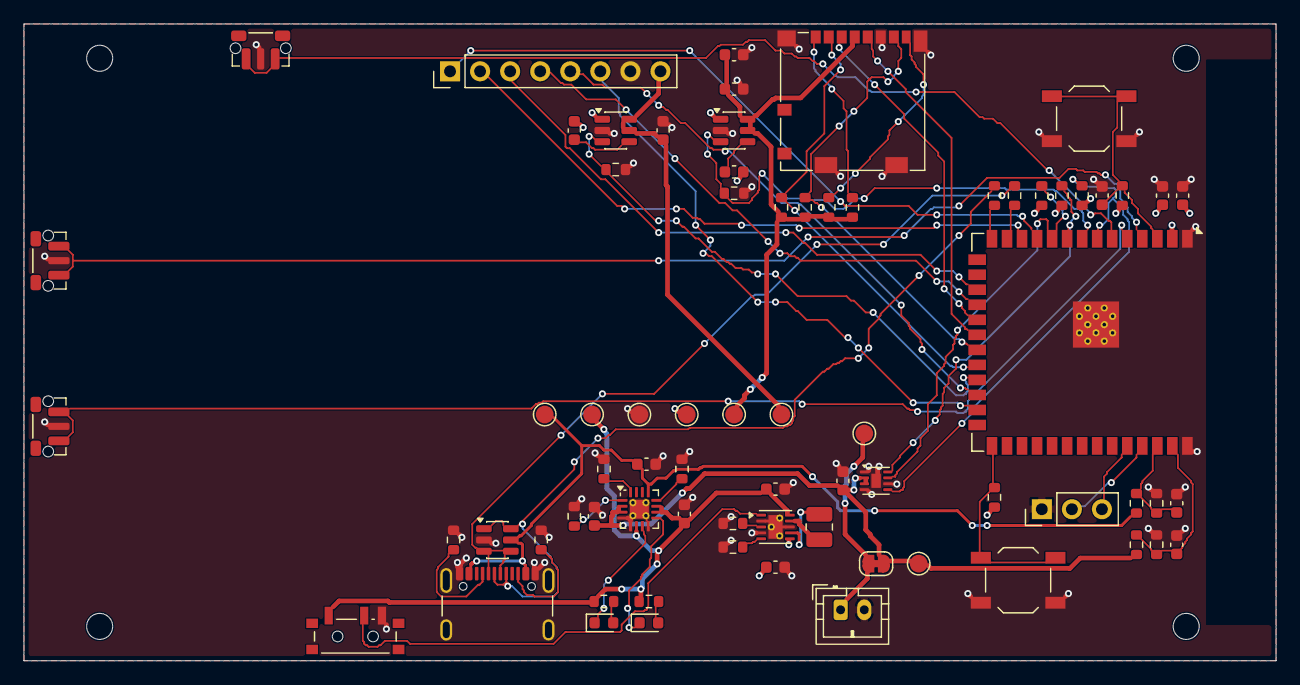
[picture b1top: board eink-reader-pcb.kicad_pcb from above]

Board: 4 copper layers, 105.8 x 53.8 mm, 76 parts (0 on the bottom side), 54 nets.

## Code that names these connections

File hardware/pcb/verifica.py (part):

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    m = esp_map()
    # USB-ul intern e doar pe GPIO19 (D−) și GPIO20 (D+)
    if m.get('ESP_DN') != 19 or m.get('ESP_DP') != 20:
        eroare(f'USB: D− pe GPIO{m.get("ESP_DN")}, D+ pe GPIO{m.get("ESP_DP")}; trebuie 19 și 20')
    # între modul și mufă câte o rezistență serie de 22–33 Ω (ghidul Espressif, USB)
    for esp, usb in (('ESP_DP', 'USB_DP'), ('ESP_DN', 'USB_DN')):
        rs = [r for r, _ in pins_on(esp) if r.startswith('R')]
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    if not ups:
        eroare('GPIO0 (BOOT) nu are rezistență spre +3V3')
    # EN: RC 10 kΩ / 1 µF, cum recomandă ghidul Espressif
    rc = sorted(PARTS[r]['value'] for r, _ in pins_on('ESP_EN') if r[0] in 'RC')
    if rc != ['10k', '1uF']:
        eroare(f'EN are {rc}; ghidul Espressif cere 10 kΩ spre 3,3 V și 1 µF spre masă')

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    """Antetul plăcii (firmware/boards/include/board_pcb_v1.h) trebuie să
    folosească exact pinii de aici: fiecare BOARD_* cu GPIO pe rețeaua cu același
    nume, fiecare semnal al modulului cu define-ul lui."""
    nume = {'BAT_ADC_GPIO': 'VBAT_SENSE', 'VBUS_SENSE_GPIO': 'VBUS_SENSE'}
    m = esp_map()
    src = open(ANTET, encoding='utf-8').read()
    vazute = set()
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
# ---------------------------------------------------------------- polaritatea
def check_polaritate():
    # LED-urile: catodul (pinul 1 al Device:LED) pe ieșirea open-drain, anodul spre VSYS prin rezistență
    for d, od in (('D1', 'PGOOD_N'), ('D2', 'CHG_N')):
        if name_of(d, '1') != 'K' or net_of(d, '1') != od:
            eroare(f'{d}: catodul nu e pe {od}')
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    # încărcătorul: /CE pe masă (încărcarea pornită), ILIM legat (altfel nu încarcă)
    if net_of('U2', '4') != 'GND':
        eroare('U2: /CE nu e pe masă, încărcarea e oprită')
    for pin, nm in (('12', 'ILIM'), ('16', 'ISET'), ('1', 'TS')):
        if not any(r.startswith('R') for r, _ in pins_on(net_of('U2', pin) or '-')):
            eroare(f'U2: {nm} nu are rezistența lui')
    # TPS22917: condensatorul CT merge la VIN (foaia TPS22917, 9.3.2)
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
